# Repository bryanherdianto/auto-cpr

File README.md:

# Auto CPR

A new Flutter project.

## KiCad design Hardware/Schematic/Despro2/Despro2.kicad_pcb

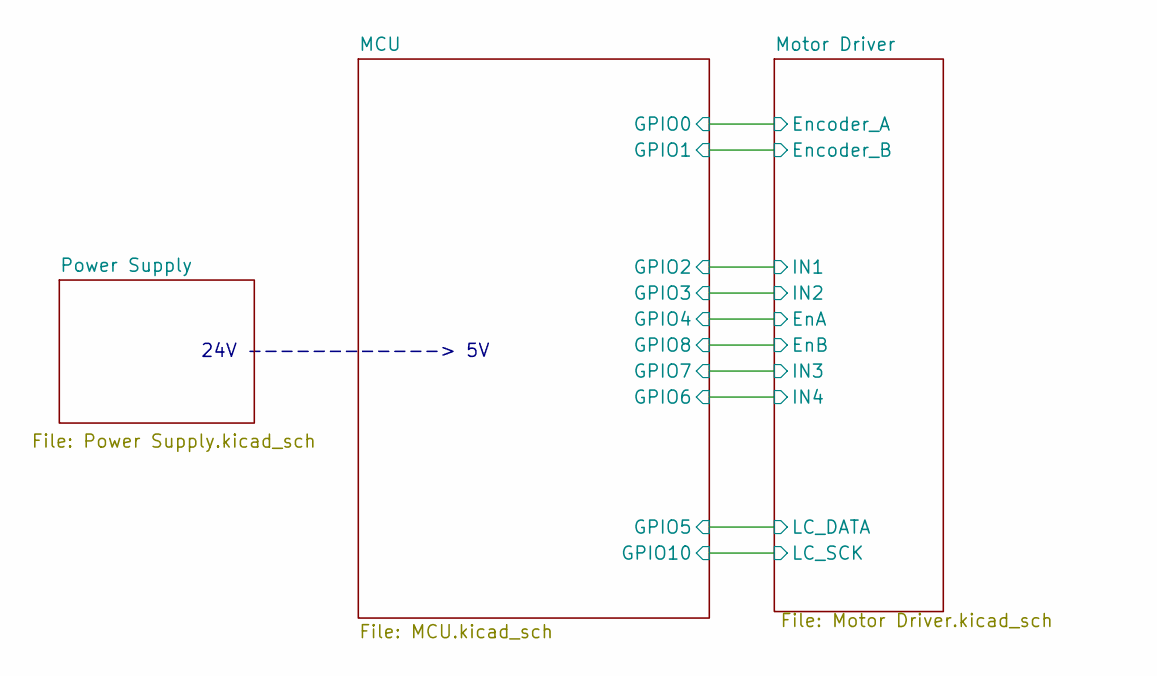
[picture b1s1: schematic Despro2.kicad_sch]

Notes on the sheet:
24V ------------> 5V

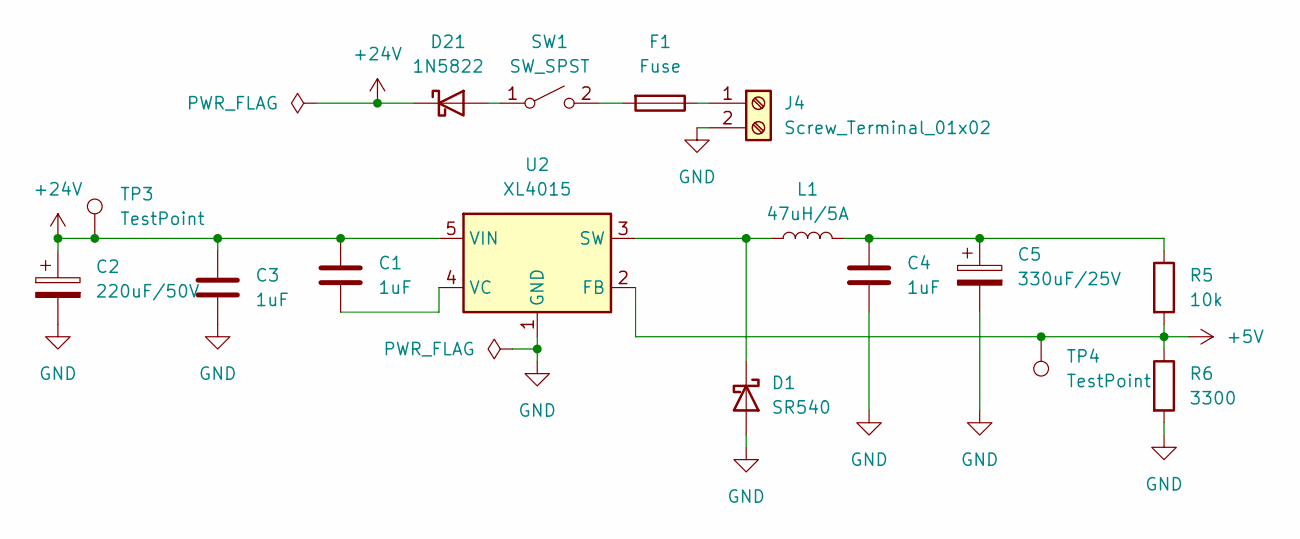
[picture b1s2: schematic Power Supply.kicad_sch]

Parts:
C1, C3, C4: 1uF; C_Disc_D5.0mm_W2.5mm_P5.00mm
C2: 220uF/50V; CP_Radial_D10.0mm_P5.00mm
C5: 330uF/25V; CP_Radial_D10.0mm_P5.00mm
D1: SR540; D_DO-201AD_P15.24mm_Horizontal
D21: 1N5822; D_DO-201AD_P15.24mm_Horizontal
F1: Fuse; Fuse-Holder-5x20
J4: Screw_Terminal_01x02; TerminalBlock_Phoenix_MKDS-1,5-2_1x02_P5.00mm_Horizontal
L1: 47uH/5A; L_Toroid_Vertical_L10.0mm_W5.0mm_P5.08mm
R5: 10k; R_Axial_DIN0411_L9.9mm_D3.6mm_P12.70mm_Horizontal
R6: 3300; R_Axial_DIN0411_L9.9mm_D3.6mm_P12.70mm_Horizontal
SW1: SW_SPST; Switch
TP3, TP4: TestPoint; PinHeader_1x01_P2.54mm_Vertical
U2: XL4015; TO-263-5_TabPin3

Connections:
+5V: R5.2, R6.1, TP4.1 (1_1), U2.2 (FB); also elsewhere on the board
+24V: C1.1, C2.1, C3.1, D21.1 (K), TP3.1 (1_1), U2.5 (VIN); also elsewhere on the board
GND: C2.2, C3.2, C4.2, C5.2, D1.2 (A), J4.2, R6.2, U2.1 (GND); also elsewhere on the board
unnamed: C4.1, C5.1, L1.2, R5.1
unnamed: D1.1 (K), L1.1, U2.3 (SW)
unnamed: D21.2 (A), SW1.1 (A)
unnamed: F1.1, J4.1
unnamed: F1.2, SW1.2 (B)
unnamed: C1.2, U2.4 (VC)

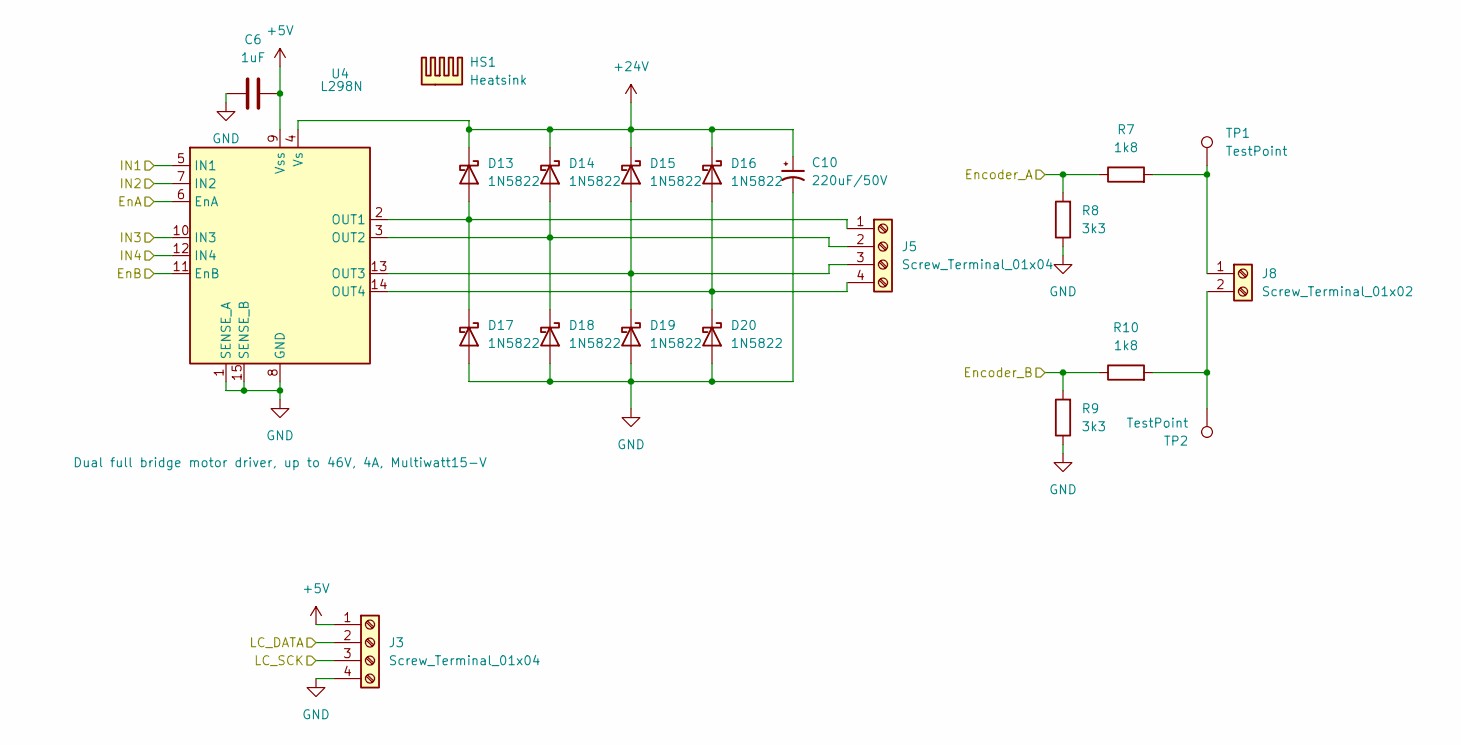
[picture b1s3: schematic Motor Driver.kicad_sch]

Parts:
C6: 1uF; C_Disc_D5.0mm_W2.5mm_P5.00mm
C10: 220uF/50V; CP_Radial_D10.0mm_P5.00mm
D13, D14, D15, D16, D17, D18, D19, D20: 1N5822; D_DO-201AD_P15.24mm_Horizontal
HS1: Heatsink
J3, J5: Screw_Terminal_01x04; TerminalBlock_Phoenix_PT-1,5-4-3.5-H_1x04_P3.50mm_Horizontal
J8: Screw_Terminal_01x02; TerminalBlock_Phoenix_MKDS-1,5-2-5.08_1x02_P5.08mm_Horizont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
R7, R10: 1k8; R_Axial_DIN0411_L9.9mm_D3.6mm_P12.70mm_Horizontal
R8, R9: 3k3; R_Axial_DIN0411_L9.9mm_D3.6mm_P12.70mm_Horizontal
TP1, TP2: TestPoint; PinHeader_1x01_P2.54mm_Vertical
U4: L298N; TO-220-15_P2.54x5.08mm_StaggerOdd_Lead4.58mm_Vertical

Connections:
+5V: C6.2, J3.1, U4.9 (Vss); also elsewhere on the board
+24V: C10.1, D13.1 (K), D14.1 (K), D15.1 (K), D16.1 (K), U4.4 (Vs); also elsewhere on the board
/MCU/GPIO0: R7.1, R8.2; also elsewhere on the board
/MCU/GPIO1: R9.2, R10.1; also elsewhere on the board
/MCU/GPIO2: U4.5 (IN1); also elsewhere on the board
/MCU/GPIO3: U4.7 (IN2); also elsewhere on the board
/MCU/GPIO4: U4.6 (EnA); also elsewhere on the board
/MCU/GPIO5: J3.2; also elsewhere on the board
/MCU/GPIO6: U4.12 (IN4); also elsewhere on the board
/MCU/GPIO7: U4.10 (IN3); also elsewhere on the board
/MCU/GPIO8: U4.11 (EnB); also elsewhere on the board
/MCU/GPIO10: J3.3; also elsewhere on the board
GND: C6.1, C10.2, D17.2 (A), D18.2 (A), D19.2 (A), D20.2 (A), J3.4, R8.1, R9.1, U4.1 (SENSE_A), U4.8 (GND), U4.15 (SENSE_B); also elsewhere on the board
unnamed: D13.2 (A), D17.1 (K), J5.1, U4.2 (OUT1)
unnamed: D14.2 (A), D18.1 (K), J5.2, U4.3 (OUT2)
unnamed: D15.2 (A), D19.1 (K), J5.3, U4.13 (OUT3)
unnamed: D16.2 (A), D20.1 (K), J5.4, U4.14 (OUT4)
unnamed: J8.1, R7.2, TP1.1 (1_1)
unnamed: J8.2, R10.2, TP2.1 (1_1)

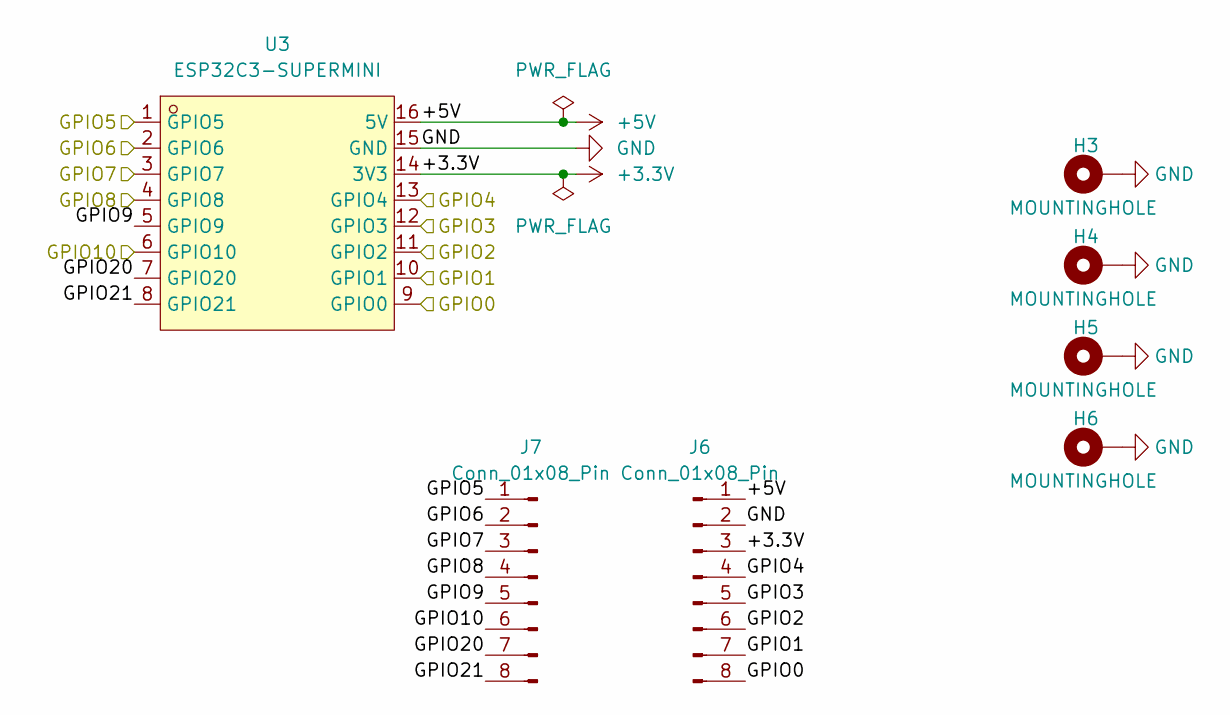
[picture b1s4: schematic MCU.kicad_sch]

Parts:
H3, H4, H5, H6: MOUNTINGHOLE; MountingHole_3.2mm_M3_Pad_Via
J6, J7: Conn_01x08_Pin; PinHeader_1x08_P2.54mm_Vertical
U3: ESP32C3-SUPERMINI; ESP32-C3-SuperMini_THT.; MPN ESP32C3-SuperMini; LCSC Part C9900147397

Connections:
+3.3V: J6.3, U3.14 (3V3)
+5V: J6.1, U3.16 (5V); also elsewhere on the board
/MCU/GPIO0: J6.8, U3.9 (GPIO0); also elsewhere on the board
/MCU/GPIO1: J6.7, U3.10 (GPIO1); also elsewhere on the board
/MCU/GPIO2: J6.6, U3.11 (GPIO2); also elsewhere on the board
/MCU/GPIO3: J6.5, U3.12 (GPIO3); also elsewhere on the board
/MCU/GPIO4: J6.4, U3.13 (GPIO4); also elsewhere on the board
/MCU/GPIO5: J7.1, U3.1 (GPIO5); also elsewhere on the board
/MCU/GPIO6: J7.2, U3.2 (GPIO6); also elsewhere on the board
/MCU/GPIO7: J7.3, U3.3 (GPIO7); also elsewhere on the board
/MCU/GPIO8: J7.4, U3.4 (GPIO8); also elsewhere on the board
/MCU/GPIO9: J7.5, U3.5 (GPIO9)
/MCU/GPIO10: J7.6, U3.6 (GPIO10); also elsewhere on the board
/MCU/GPIO20: J7.7, U3.7 (GPIO20)
/MCU/GPIO21: J7.8, U3.8 (GPIO21)
GND: H3.1 (1_1), H4.1 (1_1), H5.1 (1_1), H6.1 (1_1), J6.2, U3.15 (GND); also elsewhere on the board

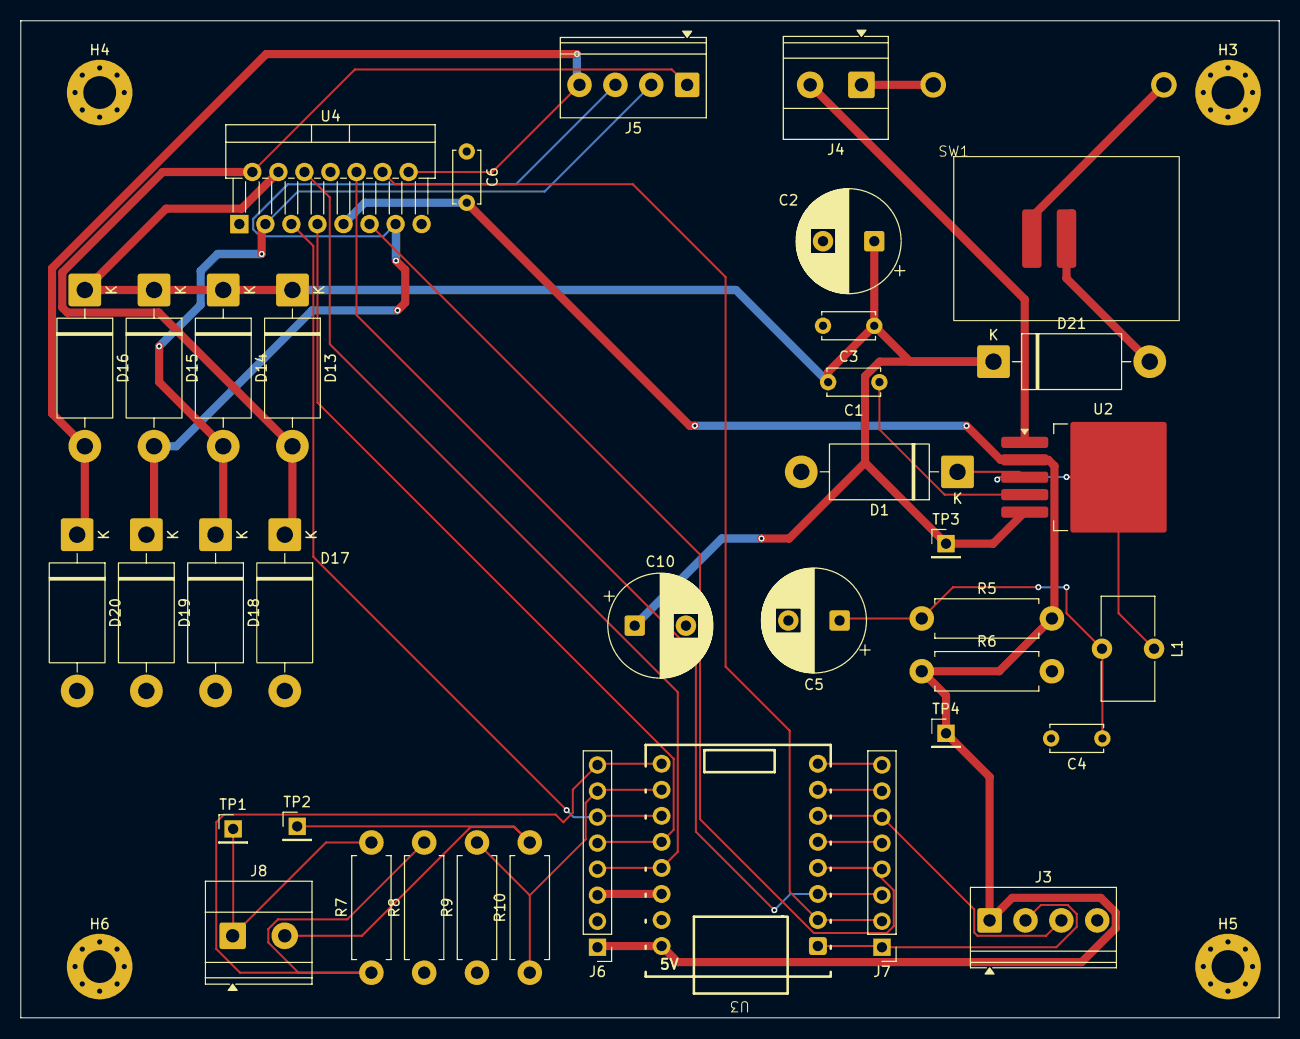
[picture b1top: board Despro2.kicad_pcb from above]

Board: 2 copper layers, 122.8 x 97.2 mm, 43 parts (0 on the bottom side), 29 nets.
